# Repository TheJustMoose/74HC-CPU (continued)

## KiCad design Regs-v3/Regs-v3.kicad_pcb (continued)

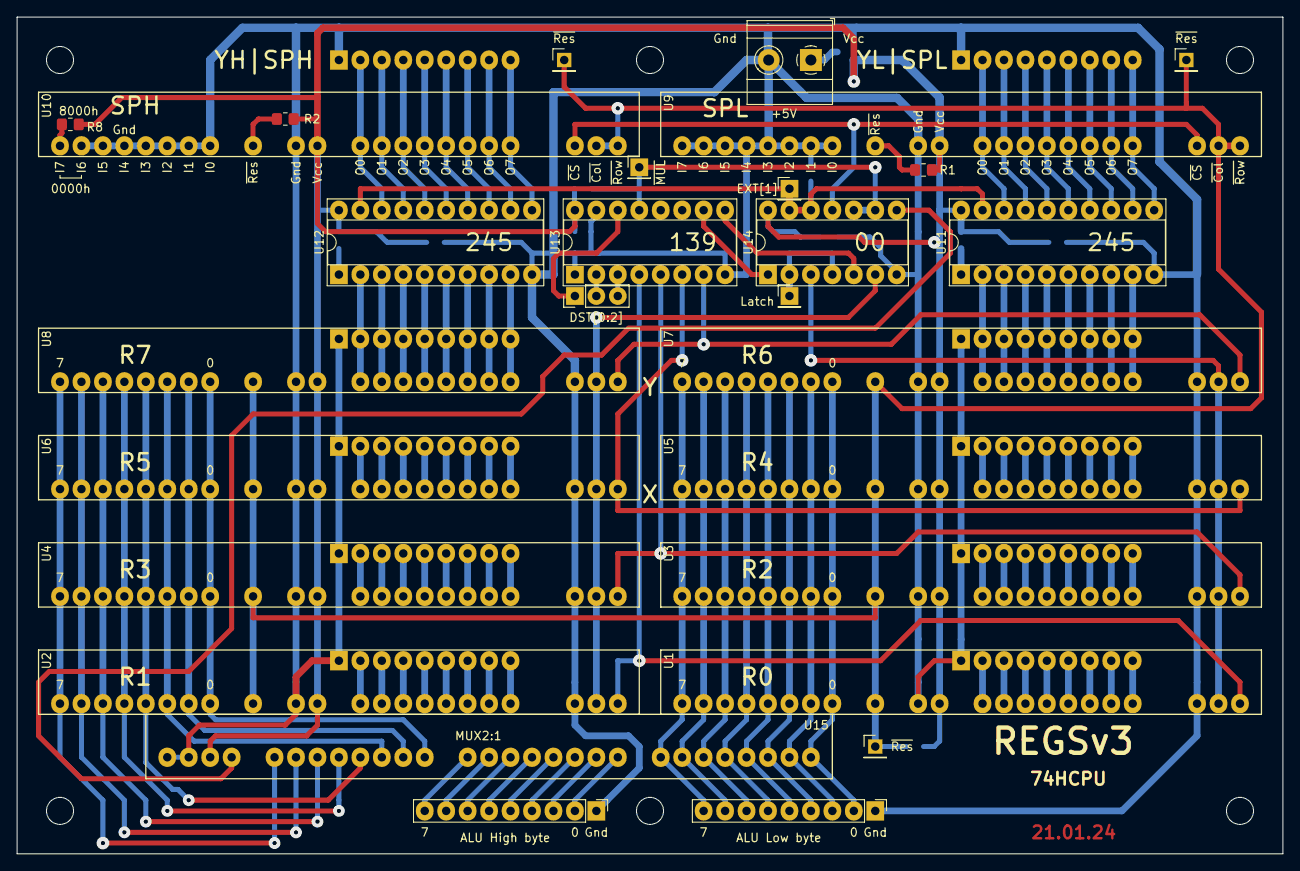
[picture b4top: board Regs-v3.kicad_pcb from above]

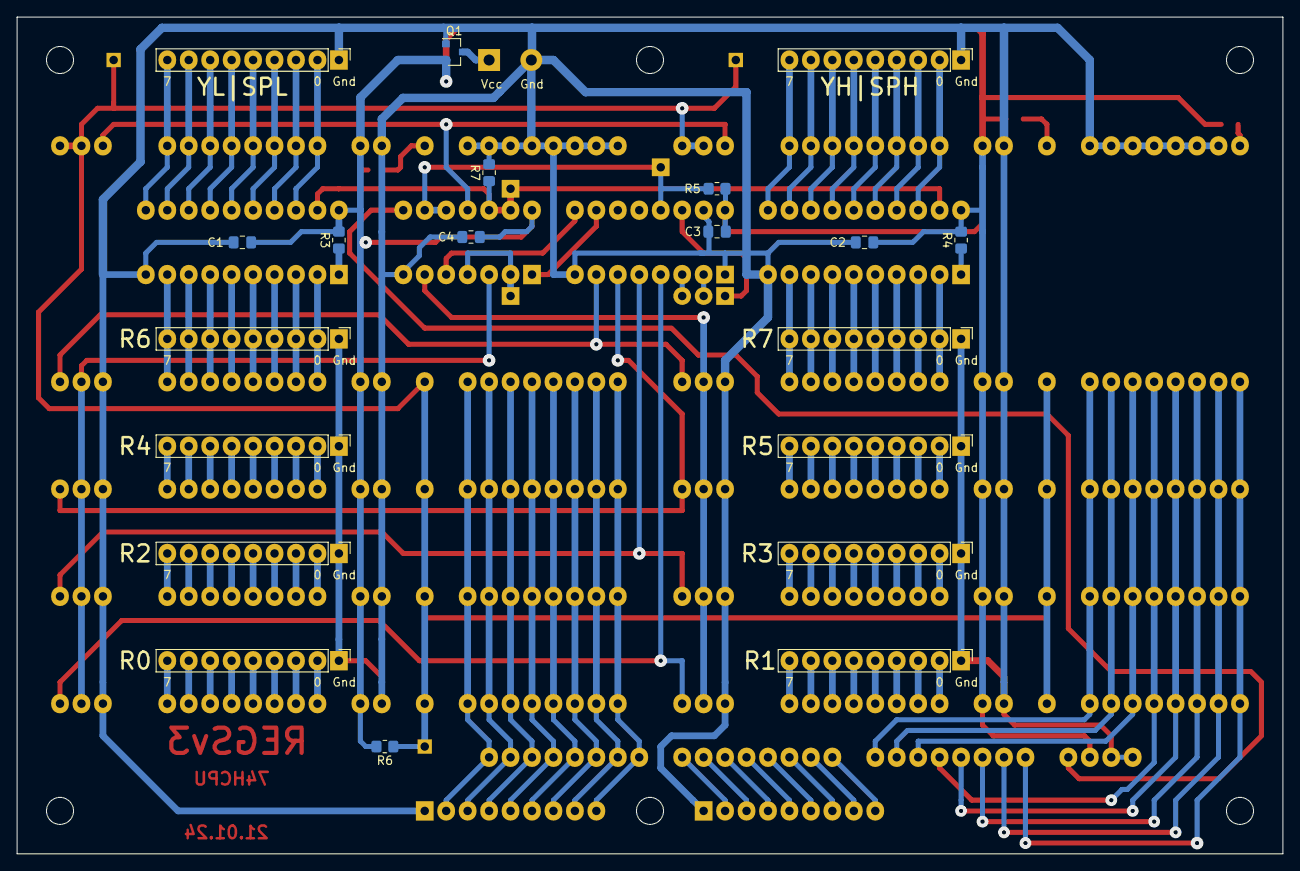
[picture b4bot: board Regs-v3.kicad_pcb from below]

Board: 2 copper layers, 149.9 x 99.1 mm, 54 parts (20 on the bottom side), 129 nets.

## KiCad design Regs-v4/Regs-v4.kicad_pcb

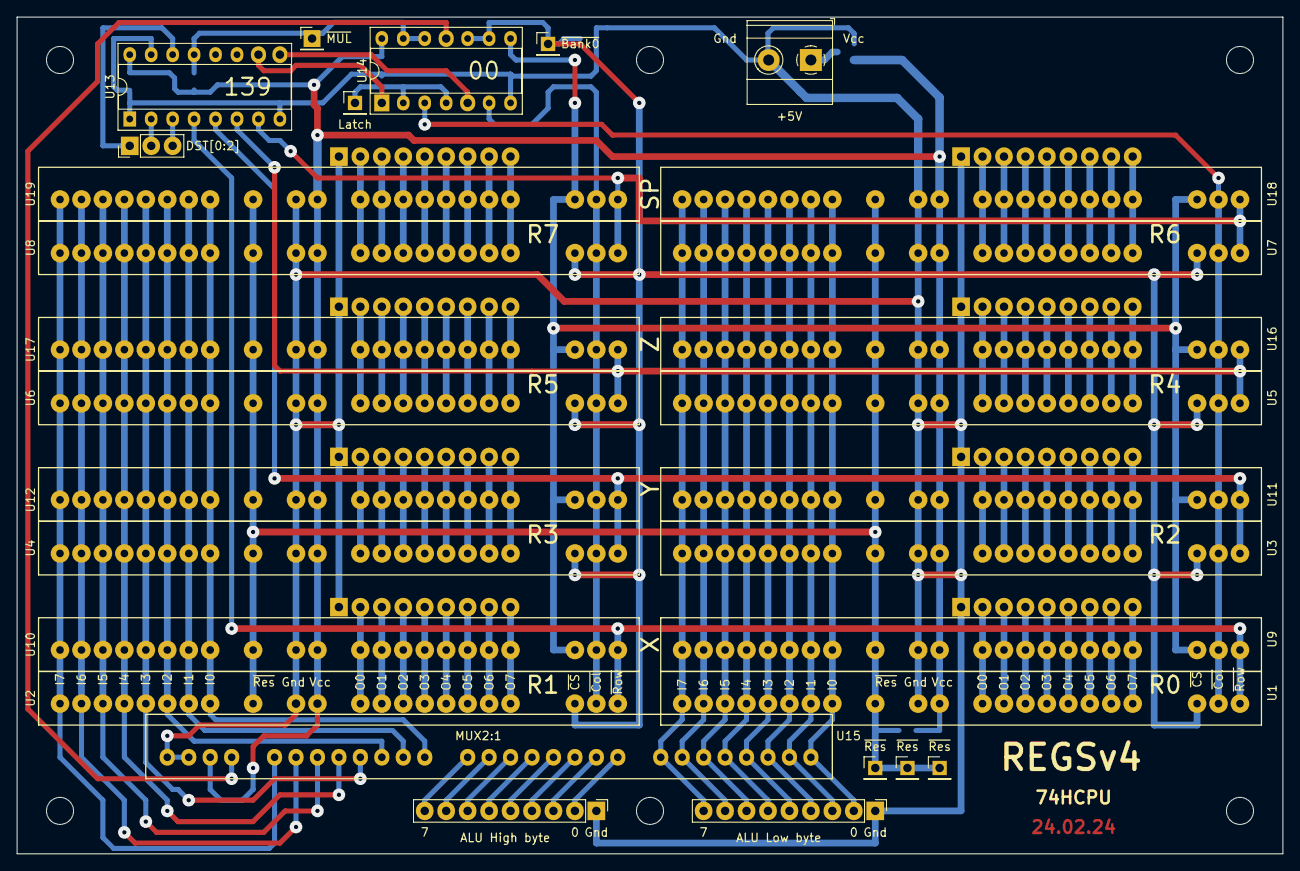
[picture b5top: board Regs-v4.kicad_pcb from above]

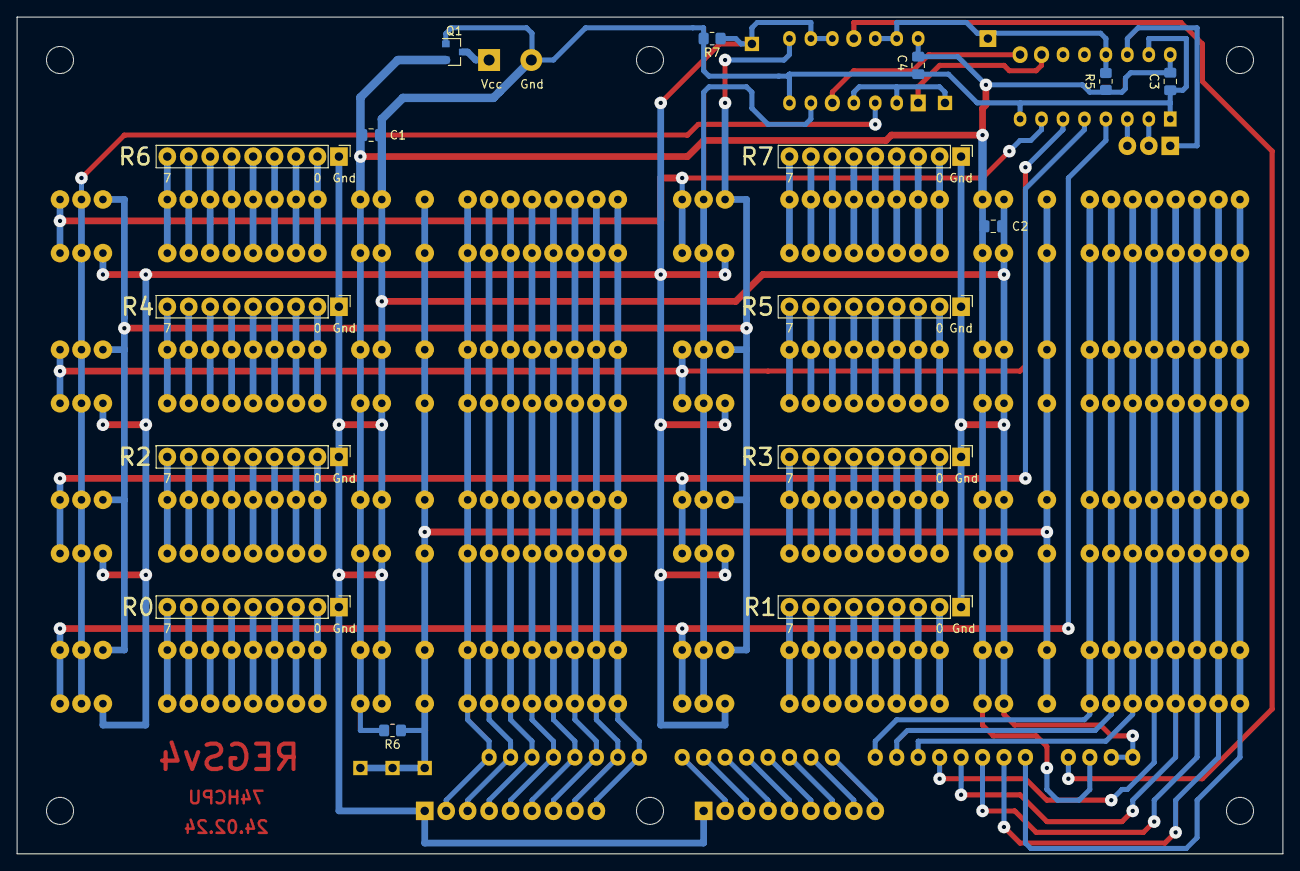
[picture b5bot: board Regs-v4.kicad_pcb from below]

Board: 2 copper layers, 149.9 x 99.1 mm, 51 parts (16 on the bottom side), 108 nets.

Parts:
C1, C2, C3, C4: 0.1uF; C_0805_2012Metric_Pad1.18x1.45mm_HandSolder
H1, H2, H3, H4, H5, H6: MountingHole; MountingHole_3.2mm_M3
J1, J2, J3, J4, J5, J6, J7, J8, J17, J18: Conn_01x09_Male; PinHeader_1x09_P2.54mm_Vertical
J11: Conn_01x03_Male; PinHeader_1x03_P2.54mm_Vertical
J12, J13, J14, J15, J19, J20: Conn_01x01_Male; PinHeader_1x01_P2.54mm_Vertical
J16: Screw_Terminal_01x02; TerminalBlock_Phoenix_MKDS-1,5-2_1x02_P5.00mm_Horizontal
Q1: IRLML5203; SOT-23
R5, R6, R7: 10k; R_0805_2012Metric_Pad1.20x1.40mm_HandSolder
U1, U2, U3, U4, U5, U6, U7, U8, U9, U10, U11, U12, U16, U17, U18, U19: REG_CNT
U13: 74LS139; DIP-16_W7.62mm_Socket
U14: 74HC00; DIP-14_W7.62mm_Socket
U15: MUX2-1; CMDwoC

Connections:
/ALU_H0: J18.2, U15.9
/ALU_H7: J18.9, U15.16
/DST[0]: J11.1, U13.14
/DST[1]: J11.2, U13.2
/DST[2]: J11.3, U13.3
/H0: U2.8, U4.8, U6.8, U8.8, U10.8, U12.8, U15.17, U17.8, U19.8
/H1: U2.7, U4.7, U6.7, U8.7, U10.7, U12.7, U15.18, U17.7, U19.7
/H2: U2.6, U4.6, U6.6, U8.6, U10.6, U12.6, U15.19, U17.6, U19.6
/H3: U2.5, U4.5, U6.5, U8.5, U10.5, U12.5, U15.20, U17.5, U19.5
/H4: U2.4, U4.4, U6.4, U8.4, U10.4, U12.4, U15.21, U17.4, U19.4
/H5: U2.3, U4.3, U6.3, U8.3, U10.3, U12.3, U15.22, U17.3, U19.3
/H6: U2.2, U4.2, U6.2, U8.2, U10.2, U12.2, U15.23, U17.2, U19.2
/H7: U2.1, U4.1, U6.1, U8.1, U10.1, U12.1, U15.24, U17.1, U19.1
/L0: J17.2, U1.8, U3.8, U5.8, U7.8, U9.8, U11.8, U15.1, U16.8, U18.8
/L1: J17.3, U1.7, U3.7, U5.7, U7.7, U9.7, U11.7, U15.2, U16.7, U18.7
/L2: J17.4, U1.6, U3.6, U5.6, U7.6, U9.6, U11.6, U15.3, U16.6, U18.6
/L3: J17.5, U1.5, U3.5, U5.5, U7.5, U9.5, U11.5, U15.4, U16.5, U18.5
/L4: J17.6, U1.4, U3.4, U5.4, U7.4, U9.4, U11.4, U15.5, U16.4, U18.4
/L5: J17.7, U1.3, U3.3, U5.3, U7.3, U9.3, U11.3, U15.6, U16.3, U18.3
/L6: J17.8, U1.2, U3.2, U5.2, U7.2, U9.2, U11.2, U15.7, U16.2, U18.2
/L7: J17.9, U1.1, U3.1, U5.1, U7.1, U9.1, U11.1, U15.8, U16.1, U18.1
/Latch: J15.1, U14.2, U14.4
/R0.0: J1.2, U1.12, U9.12
/R0.1: J1.3, U1.13, U9.13
/R0.2: J1.4, U1.14, U9.14
/R0.3: J1.5, U1.15, U9.15
/R0.4: J1.6, U1.16, U9.16
/R0.5: J1.7, U1.17, U9.17
/R0.6: J1.8, U1.18, U9.18
/R0.7: J1.9, U1.19, U9.19
/R1.0: J2.2, U2.12, U10.12
/R1.1: J2.3, U2.13, U10.13
/R1.2: J2.4, U2.14, U10.14
/R1.3: J2.5, U2.15, U10.15
/R1.4: J2.6, U2.16, U10.16
/R1.5: J2.7, U2.17, U10.17
/R1.6: J2.8, U2.18, U10.18
/R1.7: J2.9, U2.19, U10.19
/R2.0: J3.2, U3.12, U11.12
/R2.1: J3.3, U3.13, U11.13
/R2.2: J3.4, U3.14, U11.14
/R2.3: J3.5, U3.15, U11.15
/R2.4: J3.6, U3.16, U11.16
/R2.5: J3.7, U3.17, U11.17
/R2.6: J3.8, U3.18, U11.18
/R2.7: J3.9, U3.19, U11.19
/R3.0: J4.2, U4.12, U12.12
/R3.1: J4.3, U4.13, U12.13
/R3.2: J4.4, U4.14, U12.14
/R3.3: J4.5, U4.15, U12.15
/R3.4: J4.6, U4.16, U12.16
/R3.5: J4.7, U4.17, U12.17
/R3.6: J4.8, U4.18, U12.18
/R3.7: J4.9, U4.19, U12.19
/R4.0: J5.2, U5.12, U16.12
/R4.1: J5.3, U5.13, U16.13
/R4.2: J5.4, U5.14, U16.14
/R4.3: J5.5, U5.15, U16.15
/R4.4: J5.6, U5.16, U16.16
/R4.5: J5.7, U5.17, U16.17
/R4.6: J5.8, U5.18, U16.18
/R4.7: J5.9, U5.19, U16.19
/R5.0: J6.2, U6.12, U17.12
/R5.1: J6.3, U6.13, U17.13
/R5.2: J6.4, U6.14, U17.14
/R5.3: J6.5, U6.15, U17.15
/R5.4: J6.6, U6.16, U17.16
/R5.5: J6.7, U6.17, U17.17
/R5.6: J6.8, U6.18, U17.18
/R5.7: J6.9, U6.19, U17.19
/R6.0: J7.2, U7.12, U18.12
/R6.1: J7.3, U7.13, U18.13
/R6.2: J7.4, U7.14, U18.14
/R6.3: J7.5, U7.15, U18.15
/R6.4: J7.6, U7.16, U18.16
/R6.5: J7.7, U7.17, U18.17
/R6.6: J7.8, U7.18, U18.18
/R6.7: J7.9, U7.19, U18.19
/R7.0: J8.2, U8.12, U19.12
/R7.1: J8.3, U8.13, U19.13
/R7.2: J8.4, U8.14, U19.14
/R7.3: J8.5, U8.15, U19.15
/R7.4: J8.6, U8.16, U19.16
/R7.5: J8.7, U8.17, U19.17
/R7.6: J8.8, U8.18, U19.18
/R7.7: J8.9, U8.19, U19.19
/~Bank0: J14.1, R7.1, U1.20, U2.20, U3.20, U4.20, U5.20, U6.20, U7.20, U8.20, U14.9, U14.10
/~Bank1: U9.20, U10.20, U11.20, U12.20, U14.8, U16.20, U17.20, U18.20, U19.20
/~H: U2.21, U4.21, U6.21, U8.21, U10.21, U12.21, U14.6, U17.21, U19.21
/~L: U1.21, U3.21, U5.21, U7.21, U9.21, U11.21, U14.3, U16.21, U18.21
/~MUL: J12.1, R5.1, U13.13, U14.12, U14.13
/~R0: U1.22, U2.22, U9.22, U10.22, U13.4
/~R1: U3.22, U4.22, U11.22, U12.22, U13.5
/~R2: U5.22, U6.22, U13.6, U16.22, U17.22
/~R3: U7.22, U8.22, U13.7, U18.22, U19.22
/~Res: J13.1, J19.1, J20.1, R6.1, U1.9, U2.9, U3.9, U4.9, U5.9, U6.9, U7.9, U8.9, U9.9, U10.9, U11.9, U12.9, U16.9, U17.9, U18.9, U19.9
GND: C1.2, C2.2, C3.2, C4.2, J1.1, J2.1, J3.1, J4.1, J5.1, J6.1, J7.1, J8.1, J16.2, J17.1, J18.1, Q1.1, R7.2, U1.10, U2.10, U3.10, U4.10, U5.10, U6.10, U7.10, U8.10, U9.10, U10.10, U11.10, U12.10, U13.1, U13.8, U13.15, U14.7, U15.27, U15.28, U16.10, U17.10, U18.10, U19.10
unnamed: J16.1, Q1.3
unnamed: J18.3, U15.10
unnamed: J18.4, U15.11
unnamed: J18.5, U15.12
unnamed: J18.6, U15.13
unnamed: J18.7, U15.14
unnamed: J18.8, U15.15
unnamed: U13.9, U14.5
unnamed: U13.10, U14.1
unnamed: U14.11, U15.25
VCC: C1.1, C2.1, C3.1, C4.1, Q1.2, R5.2, R6.2, U1.11, U2.11, U3.11, U4.11, U5.11, U6.11, U7.11, U8.11, U9.11, U10.11, U11.11, U12.11, U13.16, U14.14, U15.26, U16.11, U17.11, U18.11, U19.11

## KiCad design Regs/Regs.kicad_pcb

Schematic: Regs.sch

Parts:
C1, C2, C3, C4, C5, C6, C7, C8: 0.1uF; C_Disc_D5.0mm_W2.5mm_P5.00mm
C9: 1uF; C_Disc_D5.0mm_W2.5mm_P5.00mm
D65, D66: LED; LED_Rectangular_W5.0mm_H2.0mm
H1, H2, H3, H4: MountingHole; MountingHole_3.2mm_M3
HL1, HL2, HL3, HL4, HL5, HL6, HL7, HL8, HL9, HL10, HL11, HL12, HL13, HL14, HL15, HL16, HL17, HL18, HL19, HL20, HL21, HL22, HL23, HL24, HL25, HL26, HL27, HL28, HL29, HL30, HL31, HL32, HL33, HL34, HL35, HL36, HL37, HL38, HL39, HL40, HL41, HL42, HL43, HL44, HL45, HL46, HL47, HL48, HL49, HL50, HL51, HL52, HL53, HL54, HL55, HL56, HL57, HL58, HL59, HL60, HL61, HL62, HL63, HL64: LED; LED_Rectangular_W5.0mm_H2.0mm
J1, J2, J3, J4, J5, J6, J7, J8: Conn_01x08_Female; PinSocket_1x08_P2.54mm_Vertical
J9: Conn_01x03_Male; PinHeader_1x03_P2.54mm_Vertical
J10, J13, J16, J18, J19: Conn_01x08_Male; PinHeader_1x08_P2.54mm_Vertical
J11, J12: Conn_01x02_Male; PinHeader_1x02_P2.54mm_Vertical
J14, J17: Conn_01x01_Male; PinHeader_1x01_P2.54mm_Vertical
J15: Screw_Terminal_01x02; TerminalBlock_Phoenix_MKDS-1,5-2-5.08_1x02_P5.08mm_Horizont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
R1, R2, R3, R4, R5: 1k; R_Axial_DIN0207_L6.3mm_D2.5mm_P10.16mm_Horizontal
RN1, RN2, RN3, RN4, RN5, RN6, RN7, RN8: R_Network08; R_Array_SIP9
SW1, SW2: SW_Push; SW_PUSH_6mm_H4.3mm
U1, U2, U3, U4, U5, U6, U7, U8: 74LS573; DIP-20_W7.62mm_Socket
U9, U15: 74LS00; DIP-14_W7.62mm_Socket
U10: 74HC238; DIP-16_W7.62mm_Socket
U11, U13, U14: 74LS257; DIP-16_W7.62mm_Socket
U12: 74LS10; DIP-14_W7.62mm_Socket

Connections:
/8\16: J14.1, R4.1, U11.1 (S), U14.1 (S), U15.1, U15.2
/Bank0-cmd: J11.1, U9.10
/Bank1-cmd: J11.2, U9.12
/C2: J12.1, U9.9, U9.13
/C3: J12.2, U10.6 (G1)
/D0: J10.1, J18.1, U1.2 (D0), U2.2 (D0), U3.2 (D0), U4.2 (D0), U11.2 (I0a)
/D1: J10.2, J18.2, U1.3 (D1), U2.3 (D1), U3.3 (D1), U4.3 (D1), U11.5 (I0b)
/D2: J10.3, J18.3, U1.4 (D2), U2.4 (D2), U3.4 (D2), U4.4 (D2), U11.14 (I0c)
/D3: J10.4, J18.4, U1.5 (D3), U2.5 (D3), U3.5 (D3), U4.5 (D3), U11.11 (I0d)
/D4: J10.5, J18.5, U1.6 (D4), U2.6 (D4), U3.6 (D4), U4.6 (D4), U14.2 (I0a)
/D5: J10.6, J18.6, U1.7 (D5), U2.7 (D5), U3.7 (D5), U4.7 (D5), U14.5 (I0b)
/D6: J10.7, J18.7, U1.8 (D6), U2.8 (D6), U3.8 (D6), U4.8 (D6), U14.14 (I0c)
/D7: J10.8, J18.8, U1.9 (D7), U2.9 (D7), U3.9 (D7), U4.9 (D7), U14.11 (I0d)
/D8: J13.1, U11.3 (I1a)
/D9: J13.2, U11.6 (I1b)
/D10: J13.3, U11.13 (I1c)
/D11: J13.4, U11.10 (I1d)
/D12: J13.5, U14.3 (I1a)
/D13: J13.6, U14.6 (I1b)
/D14: J13.7, U14.13 (I1c)
/D15: J13.8, U14.10 (I1d)
/DH0: J16.1, J19.1, U5.2 (D0), U6.2 (D0), U7.2 (D0), U8.2 (D0), U11.4 (Za)
/DH1: J16.2, J19.2, U5.3 (D1), U6.3 (D1), U7.3 (D1), U8.3 (D1), U11.7 (Zb)
/DH2: J16.3, J19.3, U5.4 (D2), U6.4 (D2), U7.4 (D2), U8.4 (D2), U11.12 (Zc)
/DH3: J16.4, J19.4, U5.5 (D3), U6.5 (D3), U7.5 (D3), U8.5 (D3), U11.9 (Zd)
/DH4: J16.5, J19.5, U5.6 (D4), U6.6 (D4), U7.6 (D4), U8.6 (D4), U14.4 (Za)
/DH5: J16.6, J19.6, U5.7 (D5), U6.7 (D5), U7.7 (D5), U8.7 (D5), U14.7 (Zb)
/DH6: J16.7, J19.7, U5.8 (D6), U6.8 (D6), U7.8 (D6), U8.8 (D6), U14.12 (Zc)
/DH7: J16.8, J19.8, U5.9 (D7), U6.9 (D7), U7.9 (D7), U8.9 (D7), U14.9 (Zd)
/DST0: J9.1, U15.12
/DST1: J9.2, U10.2 (A1)
/DST2: J9.3, U10.3 (A2)
/L0: U1.11 (Load), U10.15 (Y0), U13.2 (I0a)
/L1: U5.11 (Load), U13.4 (Za)
/L2: U2.11 (Load), U10.13 (Y2), U13.5 (I0b)
/L3: U6.11 (Load), U13.7 (Zb)
/L4: U3.11 (Load), U10.11 (Y4), U13.14 (I0c)
/L5: U7.11 (Load), U13.12 (Zc)
/L6: U4.11 (Load), U10.9 (Y6), U13.11 (I0d)
/L7: U8.11 (Load), U13.9 (Zd)
/~Bank0: D66.1 (K), U2.1 (OE), U3.1 (OE), U4.1 (OE), U6.1 (OE), U7.1 (OE), U8.1 (OE), U10.5 (~G2B), U12.6, U12.9
/~Bank1: D65.1 (K), J17.1, U12.3, U12.8
GND: C1.2, C2.2, C3.2, C4.2, C5.2, C6.2, C7.2, C8.2, C9.2, J15.2, R4.2, RN1.1 (common), RN2.1 (common), RN3.1 (common), RN4.1 (common), RN5.1 (common), RN6.1 (common), RN7.1 (common), RN8.1 (common), SW1.1, SW2.1, U1.1 (OE), U1.10 (GND), U2.10 (GND), U3.10 (GND), U4.10 (GND), U5.1 (OE), U5.10 (GND), U6.10 (GND), U7.10 (GND), U8.10 (GND), U9.7 (GND), U10.4 (~G2A), U10.8 (GND), U11.8 (GND), U11.15 (OE), U12.7 (GND), U13.8 (GND), U13.15 (OE), U14.8 (GND), U14.15 (OE), U15.7 (GND)
unnamed: C9.1, R1.1, SW2.2, U12.4
unnamed: D65.2 (A), R2.2
unnamed: D66.2 (A), R3.2
unnamed: HL1.1 (K), RN1.2 (R1)
unnamed: HL1.2 (A), J1.8, U1.12 (Q7)
unnamed: HL2.1 (K), RN1.4 (R3)
unnamed: HL2.2 (A), J1.6, U1.14 (Q5)
unnamed: HL3.1 (K), RN1.6 (R5)
unnamed: HL3.2 (A), J1.4, U1.16 (Q3)
unnamed: HL4.1 (K), RN1.8 (R7)
unnamed: HL4.2 (A), J1.2, U1.18 (Q1)
unnamed: HL5.1 (K), RN2.2 (R1)
unnamed: HL5.2 (A), J2.8, U2.12 (Q7)
unnamed: HL6.1 (K), RN2.4 (R3)
unnamed: HL6.2 (A), J2.6, U2.14 (Q5)
unnamed: HL7.1 (K), RN2.6 (R5)
unnamed: HL7.2 (A), J2.4, U2.16 (Q3)
unnamed: HL8.1 (K), RN2.8 (R7)
unnamed: HL8.2 (A), J2.2, U2.18 (Q1)
unnamed: HL9.1 (K), RN3.2 (R1)
unnamed: HL9.2 (A), J3.8, U3.12 (Q7)
unnamed: HL10.1 (K), RN3.4 (R3)
unnamed: HL10.2 (A), J3.6, U3.14 (Q5)
unnamed: HL11.1 (K), RN3.6 (R5)
unnamed: HL11.2 (A), J3.4, U3.16 (Q3)
unnamed: HL12.1 (K), RN3.8 (R7)
unnamed: HL12.2 (A), J3.2, U3.18 (Q1)
unnamed: HL13.1 (K), RN4.2 (R1)
unnamed: HL13.2 (A), J4.8, U4.12 (Q7)
unnamed: HL14.1 (K), RN4.4 (R3)
unnamed: HL14.2 (A), J4.6, U4.14 (Q5)
unnamed: HL15.1 (K), RN4.6 (R5)
unnamed: HL15.2 (A), J4.4, U4.16 (Q3)
unnamed: HL16.1 (K), RN4.8 (R7)
unnamed: HL16.2 (A), J4.2, U4.18 (Q1)
unnamed: HL17.1 (K), RN1.3 (R2)
unnamed: HL17.2 (A), J1.7, U1.13 (Q6)
unnamed: HL18.1 (K), RN1.5 (R4)
unnamed: HL18.2 (A), J1.5, U1.15 (Q4)
unnamed: HL19.1 (K), RN1.7 (R6)
unnamed: HL19.2 (A), J1.3, U1.17 (Q2)
unnamed: HL20.1 (K), RN1.9 (R8)
unnamed: HL20.2 (A), J1.1, U1.19 (Q0)
unnamed: HL21.1 (K), RN2.3 (R2)
unnamed: HL21.2 (A), J2.7, U2.13 (Q6)
unnamed: HL22.1 (K), RN2.5 (R4)
unnamed: HL22.2 (A), J2.5, U2.15 (Q4)
unnamed: HL23.1 (K), RN2.7 (R6)
unnamed: HL23.2 (A), J2.3, U2.17 (Q2)
unnamed: HL24.1 (K), RN2.9 (R8)
unnamed: HL24.2 (A), J2.1, U2.19 (Q0)
unnamed: HL25.1 (K), RN3.3 (R2)
unnamed: HL25.2 (A), J3.7, U3.13 (Q6)
unnamed: HL26.1 (K), RN3.5 (R4)
unnamed: HL26.2 (A), J3.5, U3.15 (Q4)
unnamed: HL27.1 (K), RN3.7 (R6)
unnamed: HL27.2 (A), J3.3, U3.17 (Q2)
unnamed: HL28.1 (K), RN3.9 (R8)
unnamed: HL28.2 (A), J3.1, U3.19 (Q0)
unnamed: HL29.1 (K), RN4.3 (R2)
unnamed: HL29.2 (A), J4.7, U4.13 (Q6)
unnamed: HL30.1 (K), RN4.5 (R4)
unnamed: HL30.2 (A), J4.5, U4.15 (Q4)
unnamed: HL31.1 (K), RN4.7 (R6)
unnamed: HL31.2 (A), J4.3, U4.17 (Q2)
unnamed: HL32.1 (K), RN4.9 (R8)
unnamed: HL32.2 (A), J4.1, U4.19 (Q0)
unnamed: HL33.1 (K), RN5.2 (R1)
unnamed: HL33.2 (A), J5.8, U5.12 (Q7)
unnamed: HL34.1 (K), RN5.4 (R3)
unnamed: HL34.2 (A), J5.6, U5.14 (Q5)
unnamed: HL35.1 (K), RN5.6 (R5)
unnamed: HL35.2 (A), J5.4, U5.16 (Q3)
unnamed: HL36.1 (K), RN5.8 (R7)
unnamed: HL36.2 (A), J5.2, U5.18 (Q1)
unnamed: HL37.1 (K), RN6.2 (R1)
unnamed: HL37.2 (A), J6.8, U6.12 (Q7)
unnamed: HL38.1 (K), RN6.4 (R3)
unnamed: HL38.2 (A), J6.6, U6.14 (Q5)
unnamed: HL39.1 (K), RN6.6 (R5)
unnamed: HL39.2 (A), J6.4, U6.16 (Q3)
unnamed: HL40.1 (K), RN6.8 (R7)
unnamed: HL40.2 (A), J6.2, U6.18 (Q1)
unnamed: HL41.1 (K), RN7.2 (R1)
unnamed: HL41.2 (A), J7.8, U7.12 (Q7)
unnamed: HL42.1 (K), RN7.4 (R3)
unnamed: HL42.2 (A), J7.6, U7.14 (Q5)
unnamed: HL43.1 (K), RN7.6 (R5)
unnamed: HL43.2 (A), J7.4, U7.16 (Q3)
unnamed: HL44.1 (K), RN7.8 (R7)
unnamed: HL44.2 (A), J7.2, U7.18 (Q1)
unnamed: HL45.1 (K), RN8.2 (R1)
unnamed: HL45.2 (A), J8.8, U8.12 (Q7)
unnamed: HL46.1 (K), RN8.4 (R3)
unnamed: HL46.2 (A), J8.6, U8.14 (Q5)
unnamed: HL47.1 (K), RN8.6 (R5)
unnamed: HL47.2 (A), J8.4, U8.16 (Q3)
unnamed: HL48.1 (K), RN8.8 (R7)
unnamed: HL48.2 (A), J8.2, U8.18 (Q1)
unnamed: HL49.1 (K), RN5.3 (R2)
unnamed: HL49.2 (A), J5.7, U5.13 (Q6)
unnamed: HL50.1 (K), RN5.5 (R4)
unnamed: HL50.2 (A), J5.5, U5.15 (Q4)
unnamed: HL51.1 (K), RN5.7 (R6)
unnamed: HL51.2 (A), J5.3, U5.17 (Q2)
unnamed: HL52.1 (K), RN5.9 (R8)
unnamed: HL52.2 (A), J5.1, U5.19 (Q0)
unnamed: HL53.1 (K), RN6.3 (R2)
unnamed: HL53.2 (A), J6.7, U6.13 (Q6)
unnamed: HL54.1 (K), RN6.5 (R4)
unnamed: HL54.2 (A), J6.5, U6.15 (Q4)
unnamed: HL55.1 (K), RN6.7 (R6)
unnamed: HL55.2 (A), J6.3, U6.17 (Q2)
unnamed: HL56.1 (K), RN6.9 (R8)
unnamed: HL56.2 (A), J6.1, U6.19 (Q0)
unnamed: HL57.1 (K), RN7.3 (R2)
unnamed: HL57.2 (A), J7.7, U7.13 (Q6)
unnamed: HL58.1 (K), RN7.5 (R4)
unnamed: HL58.2 (A), J7.5, U7.15 (Q4)
unnamed: HL59.1 (K), RN7.7 (R6)
unnamed: HL59.2 (A), J7.3, U7.17 (Q2)
unnamed: HL60.1 (K), RN7.9 (R8)
unnamed: HL60.2 (A), J7.1, U7.19 (Q0)
unnamed: HL61.1 (K), RN8.3 (R2)
unnamed: HL61.2 (A), J8.7, U8.13 (Q6)
unnamed: HL62.1 (K), RN8.5 (R4)
unnamed: HL62.2 (A), J8.5, U8.15 (Q4)
unnamed: HL63.1 (K), RN8.7 (R6)
unnamed: HL63.2 (A), J8.3, U8.17 (Q2)
unnamed: HL64.1 (K), RN8.9 (R8)
unnamed: HL64.2 (A), J8.1, U8.19 (Q0)
unnamed: R5.2, SW1.2, U12.10
unnamed: U10.1 (A0), U15.8
unnamed: U10.7 (Y7), U13.10 (I1d)
unnamed: U10.10 (Y5), U13.13 (I1c)
unnamed: U10.12 (Y3), U13.6 (I1b)
unnamed: U10.14 (Y1), U13.3 (I1a)
unnamed: U9.8, U12.5
unnamed: U9.11, U12.11
unnamed: U13.1 (S), U15.3, U15.13
unnamed: U15.9, U15.10, U15.11
VCC: C1.1, C2.1, C3.1, C4.1, C5.1, C6.1, C7.1, C8.1, J15.1, R1.2, R2.1, R3.1, R5.1, U1.20 (VCC), U2.20 (VCC), U3.20 (VCC), U4.20 (VCC), U5.20 (VCC), U6.20 (VCC), U7.20 (VCC), U8.20 (VCC), U9.14 (VCC), U10.16 (VCC), U11.16 (VCC), U12.14 (VCC), U13.16 (VCC), U14.16 (VCC), U15.14 (VCC)

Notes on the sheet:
if (S) Z = l1 else Z = l0
L(0) -> 8 bit mode H(1) -> 16 bit mode

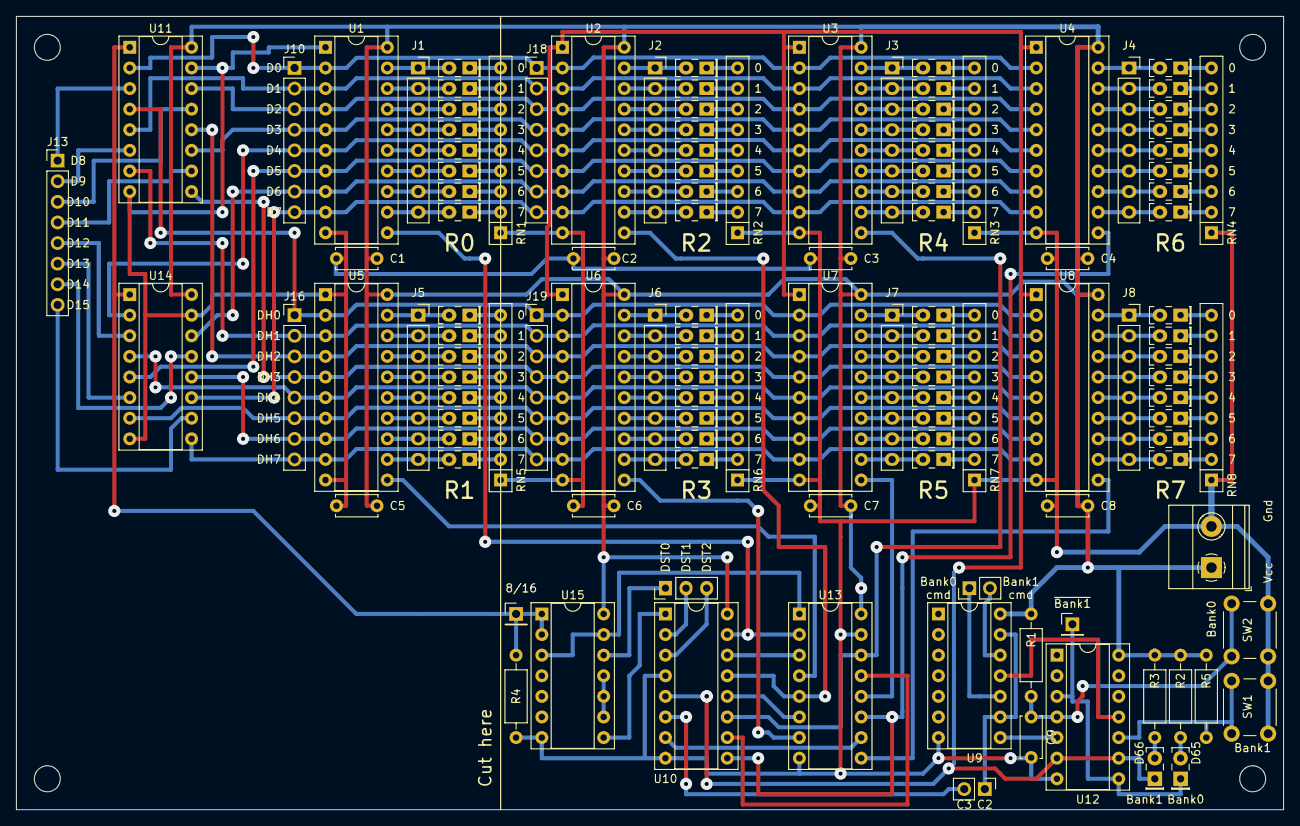
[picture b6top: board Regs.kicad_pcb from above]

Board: 2 copper layers, 156.2 x 97.8 mm, 128 parts (0 on the bottom side), 185 nets.

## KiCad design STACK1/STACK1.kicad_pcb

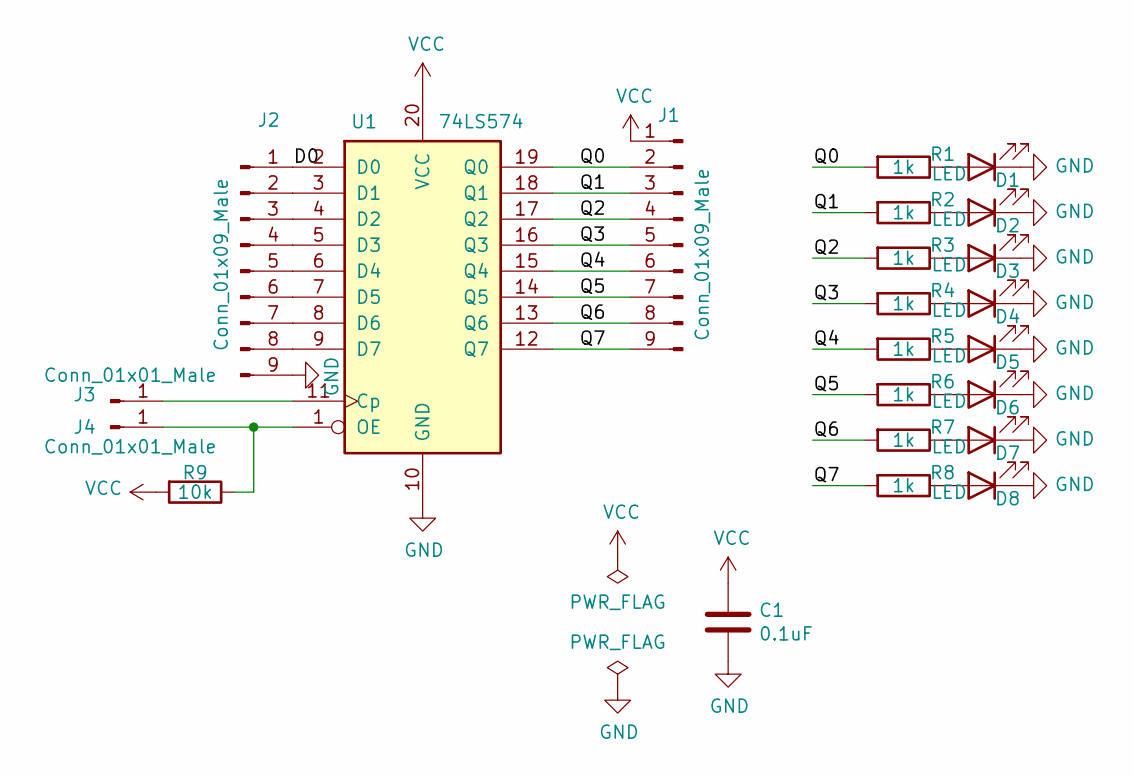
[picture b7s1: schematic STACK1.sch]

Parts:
C1: 0.1uF; C_0805_2012Metric_Pad1.18x1.45mm_HandSolder
D1, D2, D3, D4, D5, D6, D7, D8: LED; LED_0805_2012Metric_Pad1.15x1.40mm_HandSolder
J1, J2: Conn_01x09_Male; PinHeader_1x09_P2.54mm_Vertical
J3, J4: Conn_01x01_Male; PinHeader_1x01_P2.54mm_Horizontal
R1, R2, R3, R4, R5, R6, R7, R8: 1k; R_0805_2012Metric_Pad1.20x1.40mm_HandSolder
R9: 10k; R_0805_2012Metric_Pad1.20x1.40mm_HandSolder
U1: 74LS574; SO-20_12.8x7.5mm_P1.27mm

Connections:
/D0: J2.1, U1.2 (D0)
/Q0: J1.2, R1.2, U1.19 (Q0)
/Q1: J1.3, R2.2, U1.18 (Q1)
/Q2: J1.4, R3.2, U1.17 (Q2)
/Q3: J1.5, R4.2, U1.16 (Q3)
/Q4: J1.6, R5.2, U1.15 (Q4)
/Q5: J1.7, R6.2, U1.14 (Q5)
/Q6: J1.8, R7.2, U1.13 (Q6)
/Q7: J1.9, R8.2, U1.12 (Q7)
GND: C1.2, D1.1 (K), D2.1 (K), D3.1 (K), D4.1 (K), D5.1 (K), D6.1 (K), D7.1 (K), D8.1 (K), J2.9, U1.10 (GND)
unnamed: D1.2 (A), R1.1
unnamed: D2.2 (A), R2.1
unnamed: D3.2 (A), R3.1
unnamed: D4.2 (A), R4.1
unnamed: D5.2 (A), R5.1
unnamed: D6.2 (A), R6.1
unnamed: D7.2 (A), R7.1
unnamed: D8.2 (A), R8.1
unnamed: J2.2, U1.3 (D1)
unnamed: J2.3, U1.4 (D2)
unnamed: J2.4, U1.5 (D3)
unnamed: J2.5, U1.6 (D4)
unnamed: J2.6, U1.7 (D5)
unnamed: J2.7, U1.8 (D6)
unnamed: J2.8, U1.9 (D7)
unnamed: J3.1, U1.11 (Cp)
unnamed: J4.1, R9.1, U1.1 (OE)
VCC: C1.1, J1.1, R9.2, U1.20 (VCC)

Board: 2 copper layers, 23 parts (2 on the bottom side), 28 nets, no tracks yet.
